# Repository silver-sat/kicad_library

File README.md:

# kicad_library

# Shared libraries for SilverSat-specific parts

This repository contains shared libraries for custom KiCAD parts developed for the SilverSat PC board designs. There are two libraries in this repository:
  SilverSat_symbols.lib :  custom schematic symbols used while drawing schematics
  SilverSat_footprints.pretty : custom footprints used in PCB layouts.
  
  Note that SilverSat_symbols.lib is a single file containing all of the custom symbols.  SilverSat_footprints.pretty is a folder, and each custom footprint is a separate file in this folder.
  
  ## Installing the SilverSat Libraries
  1) If you haven't already, set up a location on your computer for KiCAD libraries in your Documents folder, at Documents\KiCAD\Libraries.
  2) Create a folder specifically for the SilverSat libraries: Documents\KiCAD\Libraries\SilverSat.
  3) On the github website (https://github.com/silver-sat/kicad_library), make sure you have selected the 'main' branch of this repository.
  4) If you have git on your computer, clone this repository and store it locally in Documents\KiCAD\Libraries\SilverSat.
  5) If you don't have git, hit the green 'Code' button and select 'Download ZIP'. Download the zip file to Documents\KiCAD\Libraries\SilverSat and unzip it (this will add '-main' to the name of the folder)
  6) Open KiCAD. From the main project window, select the Preferences pulldown, and from there select Manage Symbol Libraries.
  7) Make sure you’re on the Global Libraries tab. Hit the button that looks like file folder (‘Add Existing Library to Table’).
  8) Navigate to your recently stored kicad_library folder, and select ‘SilverSat_symbols.lib’ and hit OK.  SilverSat_symbols should now appear in the list of libraries. 
  9) Hit OK again to close out the 'Manage Symbol Libraries' window.
  10) Go back to the KiCAD main window. Select the Preferences pulldown, and select Manage Footprint Libraries.
  11) Make sure you’re on the Global Libraries tab. Hit the button that looks like file folder (‘Add Existing Library to Table’).
  12) Navigate to your recently stored kicad_library folder, and select the ‘SilverSat_footprints.pretty’ folder, and hit OK. Here, you're selecting an entire folder, not just a single file. 
  13) Hit OK again to close out the 'Manage Footprint Libraries' window.
  14) Go open a KiCAD schematic. Hit the Place Symbol icon, and make sure you can now see the SilverSat_symbols library.

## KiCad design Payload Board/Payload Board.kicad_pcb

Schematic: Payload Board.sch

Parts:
C1, C2, C3, C5, C7, C8, C9: .1uF; C_0603_1608Metric
C4, C6: 33pF; C_0603_1608Metric
H1, H2: Conn_02x26_Odd_Even; TheBus2x26
J1: Conn_01x08_Male; PinHeader_1x08_P2.54mm_Vertical
R1, R2, R3, R4, R5, R6, R7: 10 kohm; R_0603_1608Metric
R8: 453; R_0603_1608Metric
U1: RaspberryPiZero(v1.1); Raspberry_Pi_Zero_Socketed_THT_FaceDown_MountingHoles
U2, U3, U4: 74LVC1G07MDCKREPG4; SOT-353_SC-70-5
U5: MAX3100; QSOP-16_3.9x4.9mm_P0.635mm
U6: SN74CB3Q3306A; TSSOP-8_4.4x3mm_P0.65mm
U7: uCamIII; UCAM-III
U8: SN65HVD70D; SOIC-14_3.9x8.7mm_P1.27mm
Y1: 3.5864 MHz1; Crystal_SMD_HC49-SD_HandSoldering

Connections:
+3V3: C1.1, C2.1, C3.1, C5.1, C7.2, C9.1, J1.2, R1.1, R2.2, R3.2, R4.1, R5.2, R7.1, U1.1, U1.17, U2.5, U3.5, U4.5, U5.16, U6.8, U8.13, U8.14
+5V: H1.27, H1.29, J1.1, U1.2, U1.4, U7.1
GND: C1.2, C2.2, C3.2, C4.2, C5.2, C6.2, C7.1, C9.2, H1.13, H1.42, H1.46, H1.50, H2.8, H2.15, H2.29, H2.30, H2.31, H2.32, J1.8, R6.1, U1.6, U1.9, U1.14, U1.20, U1.25, U1.30, U1.39, U2.3, U3.3, U4.3, U5.8, U6.4, U7.4, U8.6, U8.7
unnamed: C4.1, U5.9, Y1.1
unnamed: C6.1, U5.10, Y1.2
unnamed: C8.1, H1.8, U8.11
unnamed: C8.2, R8.2
unnamed: H1.5, U8.9
unnamed: H1.6, R8.1, U8.12
unnamed: H1.7, U8.10
unnamed: H1.45, U6.3
unnamed: H1.51, U6.6
unnamed: H2.9, U2.4
unnamed: H2.10, J1.5, R1.2, U1.40
unnamed: H2.11, U3.4
unnamed: H2.12, J1.4, R2.1, U1.38
unnamed: H2.13, U4.4
unnamed: H2.14, J1.3, R3.1, U1.36
unnamed: J1.6, U1.8, U8.5
unnamed: J1.7, U1.10, U8.2
unnamed: R4.2, U1.22, U6.1, U6.7
unnamed: R5.1, U5.7
unnamed: R6.2, U8.3
unnamed: R7.2, U8.4
unnamed: U1.3, U6.2
unnamed: U1.5, U6.5
unnamed: U1.11, U4.2
unnamed: U1.13, U3.2
unnamed: U1.15, U2.2
unnamed: U1.16, U7.5
unnamed: U1.19, U5.3
unnamed: U1.21, U5.2
unnamed: U1.23, U5.1
unnamed: U5.14, U7.2
unnamed: U5.15, U7.3

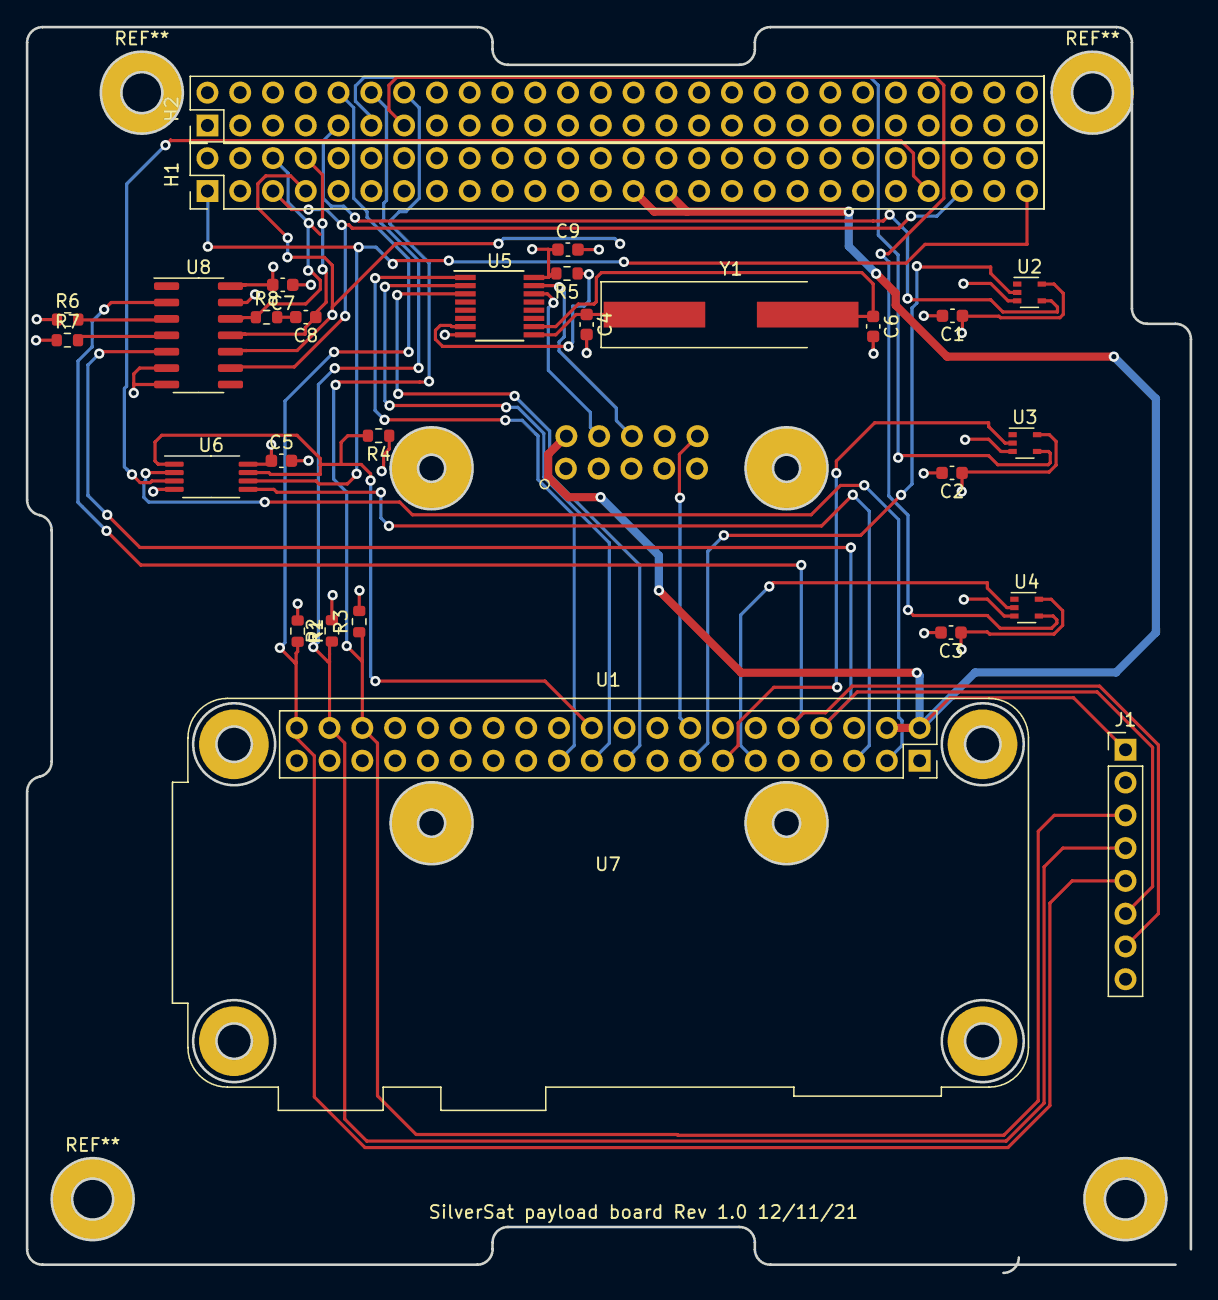
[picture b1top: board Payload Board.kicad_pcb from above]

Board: 4 copper layers, 90.2 x 96.5 mm, 29 parts (0 on the bottom side), 35 nets.

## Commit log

2021-12-05 Add files via upload
    Initial commit of the symbol library
2022-01-01 Update Payload Kicad
2022-01-14 updated to test file upload to Github.
2022-01-14 Testing github upload
2022-01-15 Add files via upload
    Added components from the Payload board
2022-01-16 Added the BD2286G
2022-01-16 Add files via upload
    I added Payload Parts to the Library
2022-01-16 Combined the last two commits
    Added the BD2268G to the Payload board parts.
2022-01-16 Added install instructions to the README.md
2022-03-05 Trying to put in 5v5
2022-04-09 Added TPS2105
2022-06-02 Added TG2016SMN TCXO and ported to KiCad 6
2022-06-02 Fix designator error
2022-07-09 DFN footprint
    Footprint for TPS22965
2022-07-10 Update TheBus2x26.kicad_mod
    Fixed duplicated pin and redundant courtyard traces
2022-07-10 Update DFN-8-1EP_2.1x2.1mm_P0.5mmx0.25mm_EP0.8x1.6mm.kicad_mod
    Fixed ground paddle to tie to ground
2022-07-20 Update SilverSat_symbols.kicad_sym
    Added molex connector
2022-07-25 Add approximate HMC452ST89 footprints Issues - Pad 4 does not align with the datasheet's shape specifications. It needs a custom shape primitive.
2022-07-25 RF Shield
    Added Masach RF shield MS355-10
2022-07-25 Update MS355-10_Masach_Shield.kicad_mod
    Changed traces into pads to try to eliminate the DRC error
2022-07-30 Add silkscreen SilverSat logo
2022-08-02 Small changes to one footprint Corrected art problems in SilverSat logo footprint
2022-08-02 Add MS355 cover symbol
2022-08-05 Add SilverSat footprint source
2022-08-05 Add SilverSat patch
2022-08-06 Extract HMC452ST89 pad from datasheet Issues KiCad does not recognize the fill in the polygon and instead renders an open shape.
2022-08-10 Add ground symbol
2022-08-11 Update HMC452ST89 center pad
2022-08-13 3d models
    Added folder for 3d models. Added 3d models for some parts on radio board
2022-08-14 Update HMC452ST89.kicad_mod
    Updated HMC452 to have pads per manufacturer preferred design
2024-04-06 Update to KiCad 8 and add custom fiducial
2024-04-24 Update TheBus2x26.kicad_mod
    Remove the courtyard that was causing much DRC consternation
2024-06-01 Change text size
2024-06-13 3d models
    Added some 3d models to support the payload board
